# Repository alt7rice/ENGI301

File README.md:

# ENGI301
Repository for ENGI301 coursework

This repository now includes a simple calculator code and a way to turn on the USR3 LED on the pocketbeagle.
This repository has code to make an LED blink.

This repository also includes the code to run a device that can alert a user that the have been sitting for too long (Project_01).

This repository includes a possible PCB design for the device designed in Project_01 (Project_02) further description is at the bottom of this Readme.    
      
      Below is the Story for the Body Position Sensor .
During this pandemic, we have all been sitting at home and not getting the exercise that we need. Doctors recommend that we stand for at least 4 hours a day. This device was created to be able to detect your body position to alert you when you need to stand. This device could be useful when working from home or in the office to act as a friendly reminder and combat a sedentary lifestyle.

Using an accelerometer/gyroscope (MPU-6050) and python, the body position was determined. Since the device is attached to the leg using velcro straps, the acceleration due to gravity can be used to differentiate between sitting and standing. When gravity is in the z-direction, the user is sitting and when gravity is in the y-direction, the user is standing.  To determine when the user is walking, the magnitude of the acceleration in the x, y, and z-directions had to be above 6 m/s^2. This calculation was based on the project by Ashish Choudhary where they create a Portable Step Counter using ATtiny85 and MPU6050. When The position was shown on an LCD screen (Adafruit RGB backlight positive LCD 16x2). If the user has been sitting for longer than an hour, the LCD screen will display the message, "You need to stand!!!" In addition to the message, a mini vibration motor will vibrate repeatedly until the user stands. As soon as the user stands, the motor stops and the message changes to, "Standing". The clock will begin again to count down the hour once the user sits again. The device is powered using a mini portable phone charger, and the microcontroller that regulates this system is a PocketBeagle. 

Overall, this device is functional in alerting the user that they have been sitting for an extended period of time. However, there is still room for improvements. The detection of body position is not effective in distinguishing between standing and walking. This problem can be addressed through an adjustment of the cutoff values after gaining a better understanding of the data outputted by the accelerometer/gyroscope. Additionally, the device is very bulky for a wearable so next steps would include making a printed circuit board to miniaturize the device.

Implementation instructions:

Initialize the PocketBeagle by doing the following:
1.  Connect the PocketBeagle to the internet
2. sudo apt-get update
3. sudo apt-get install build-essential python-dev python-setuptools python-smbus -y
4. git clone https://github.com/adafruit/adafruit-beaglebone-io-python
5. sudo pip3 install --upgrade Adafruit_BBIO

Setting up the hardware:
1. Download Adafruit library for the LCD screen
2. Connect LCD screen following these instructions 
   Note: Although, the LCD screen in the instructions only has 16 pins, the pins all match up to the 18 pin one used in this project. The only difference is that pin 16, 17, and 18 can be grounded in any combination, with at least one of them grounded, to produce a variety colors for the backlight.
3. Test the LCD screen using the rgb_lcd_test.py file
4. Download Adafruit library for MPU6050 
5. Connect Vcc to 3.3V
6. Connect GND to ground
7. Connect SCL to Pin 2_9 on PocketBeagle (the corresponding I2C bus) and a pull up resistor (1 kOhm) to 3.3V
8. Connect SDA to Pin 2_11 on Pocketbeagle (the corresponding I2C bus) and a pull up resistor (1 kOhm) to 3.3V
9. Test the accelerometer/gyroscope using the IMU_test.py file
10. Connect one side wire of the the mini vibrating motor to Pin P2_1 and the other wire to ground. (May need to solder wires on to the mini vibrating motor to make the wires long enough to make the connections.)
11. Connect one button pin to Pin P2_1 with a pull up resistor from this node to 5V.
12. Connect the other pin of the button to ground.

After the hardware is set up, then the BodyPosition.py file can be run and the device can be used. On Cloud 9, the device was made to run when it is connected to power using the cron functionality. 

Here is a link to the hackster page for this project:
https://www.hackster.io/431666/body-position-sensing-with-an-accelerometer-gyroscope-5139e5

      PCB Design
This PCB was designed to mimic the breadboard of the initial construction. Amendments were made to have more than one mini vibration motor so that the vibration could be more intense when alerting the user when to stand. The mini motors are also at the back of the PCB board so it is against the leg of the user when it is strapped on. Additionally, the IMU is put in the middle of the board so that it can better detect the changes in body position. Other minor connection changes were also made so that there was easier formation of traces on the PCB, but none require pin reconfigurations. The docs folder include more information about the board like the schematic and board pdfs and the Bill of Materials from eagle. In addition to that, the project 2 folder has the files directly from eagle including the library, board, and schematic.

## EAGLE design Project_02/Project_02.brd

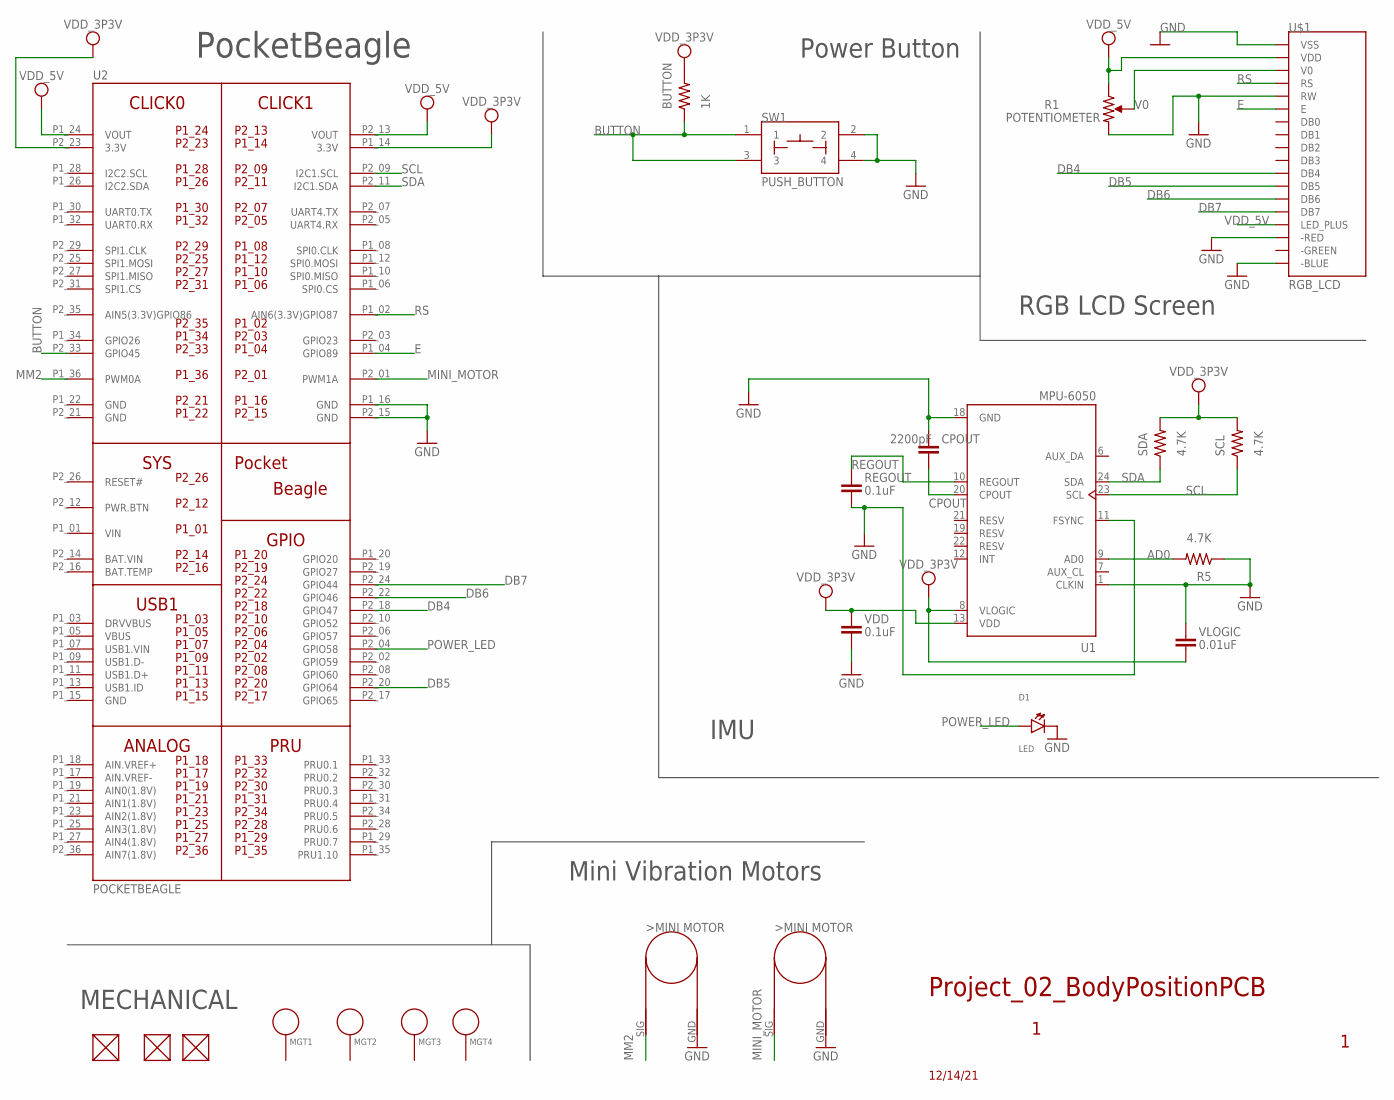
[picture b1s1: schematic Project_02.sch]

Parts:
BUTTON: 1K; R0402
CPOUT: 2200pF; C0603
D1: LED; EIA-STD
FUD1, FUD2, FUD3: FIDUCIAL; FIDUCIAL_40MIL
M1, M2: MINI_MOTOR
MGT1, MGT2, MGT3, MGT4: MOUNTING_HOLE
R1: POTENTIOMETER; POT-PO90S
R5: 4.7K; R0402
REGOUT: 0.1uF; C0603
SCL: 4.7K; R0402
SDA: 4.7K; R0402
SW1: PUSH_BUTTON; BUTTON_12.5MM
U1: MPU-6050
U2: POCKETBEAGLE
U$1: RGB_LCD
VDD: 0.1uF; C0603
VLOGIC: 0.01uF; C0603

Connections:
AD0: R5.2, U1.9 (AD0)
BAT.VIN: U2.P2_14 (BAT.VIN)
BUTTON: BUTTON.1, SW1.1, SW1.3, U2.P2_33 (GPIO45)
CPOUT: CPOUT.2, U1.20 (CPOUT)
DB4: U2.P2_18 (GPIO47), U$1.DB4
DB5: U2.P2_20 (GPIO64), U$1.DB5
DB6: U2.P2_22 (GPIO46), U$1.DB6
DB7: U2.P2_24 (GPIO44), U$1.DB7
E: U2.P1_04 (GPIO89), U$1.E
GND: CPOUT.1, D1.CATHODE, M1.GND, M2.GND, R1.CW, R5.1, REGOUT.2, SW1.2, SW1.4, U1.1 (CLKIN), U1.11 (FSYNC), U1.18 (GND), U2.P1_16 (GND), U2.P1_22 (GND), U2.P2_15 (GND), U2.P2_21 (GND), U$1.-BLUE, U$1.-RED, U$1.RW, U$1.VSS, VDD.2, VLOGIC.1
MINI_MOTOR: M1.SIG (PWM), U2.P2_01 (PWM1A)
MM2: M2.SIG (PWM), U2.P1_36 (PWM0A)
POWER_LED: D1.ANODE, U2.P2_04 (GPIO58)
REGOUT: REGOUT.1, U1.10 (REGOUT)
RS: U2.P1_02 (AIN6(3.3V)GPIO87), U$1.RS
SCL: SCL.1, U1.23 (SCL), U2.P2_09 (I2C1.SCL)
SDA: SDA.1, U1.24 (SDA), U2.P2_11 (I2C1.SDA)
V0: R1.S, U$1.V0
VDD_3P3V: BUTTON.2, SCL.2, SDA.2, U1.8 (VLOGIC), U1.13 (VDD), U2.P1_14 (3.3V), U2.P2_23 (3.3V), VDD.1, VLOGIC.2
VDD_5V: R1.CCW, U2.P1_24 (VOUT), U2.P2_13 (VOUT), U$1.LED_PLUS, U$1.VDD
VIN: U2.P1_01 (VIN)

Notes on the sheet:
MECHANICAL
PocketBeagle
Power Button
RGB LCD Screen
IMU
Mini Vibration Motors
Project_02_BodyPositionPCB
12/14/21

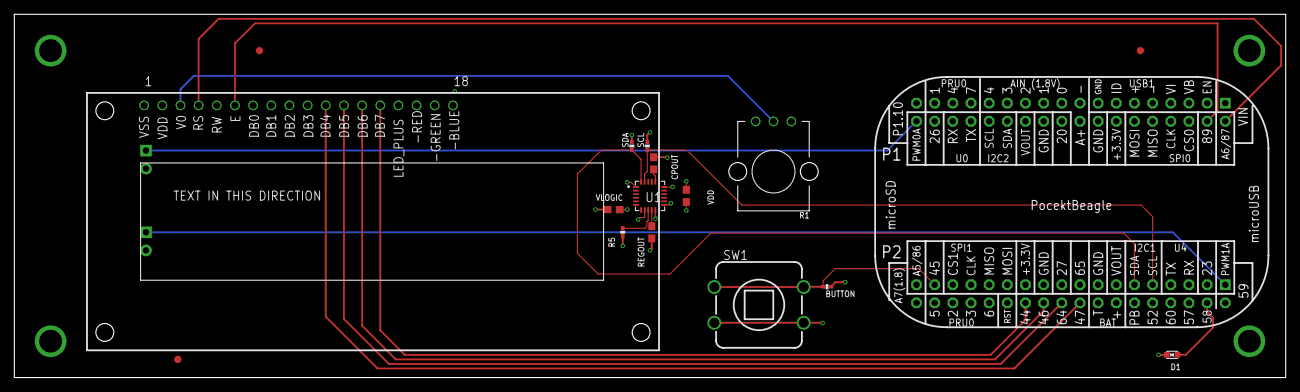
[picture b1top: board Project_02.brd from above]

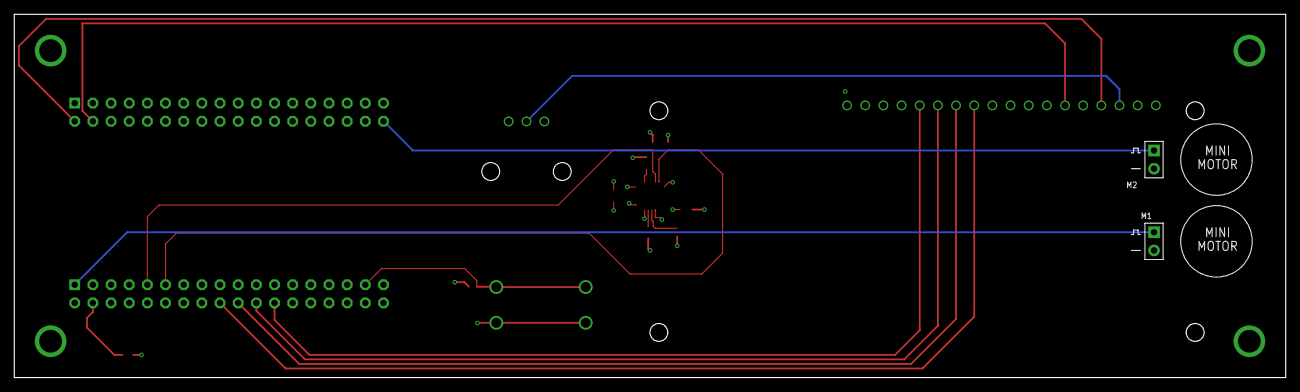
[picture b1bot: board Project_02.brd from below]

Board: 4 copper layers, 177.8 x 50.8 mm, 23 parts (2 on the bottom side), 19 nets.

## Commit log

2021-10-05 Homework 4 Question 2
2021-10-05 Homework 4 Question 1
2021-10-14 Create test
2021-11-08 adding project files
